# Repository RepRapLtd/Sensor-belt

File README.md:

# Sensor-belt

Device to allow the sense of touch to extend beyond the body.

WIP...

See here for initial details:
  
  https://reprapltd.com/2016/11/15/extra-senses/

Licence: GPL.

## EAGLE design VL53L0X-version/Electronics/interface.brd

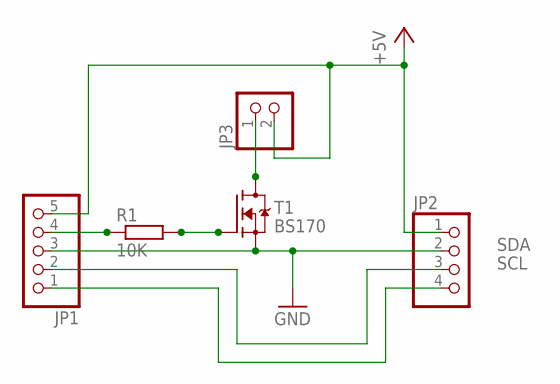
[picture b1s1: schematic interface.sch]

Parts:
JP1: PINHD-1X5; 1X05
JP2: PINHD-1X4; 1X04
JP3: PINHD-1X2; 1X02
R1: 10K; R0805
T1: BS170; SOT23

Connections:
+5V: JP1.5, JP2.1, JP3.2
GND: JP1.3, JP2.2, T1.2 (S)
unnamed: JP1.4, R1.1
unnamed: R1.2, T1.1 (G)
unnamed: JP3.1, T1.3 (D)
unnamed: JP1.2, JP2.3
unnamed: JP1.1, JP2.4

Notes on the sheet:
SDA
SCL

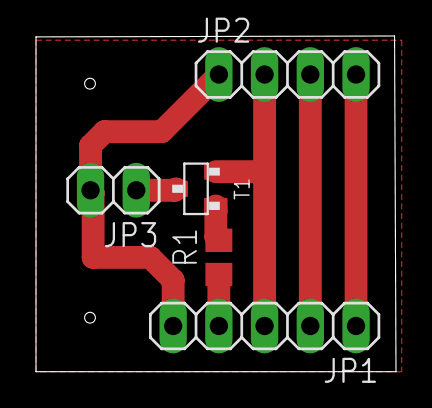
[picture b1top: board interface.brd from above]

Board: 2 copper layers, 20.0 x 18.6 mm, 5 parts (0 on the bottom side), 7 nets.

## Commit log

2016-11-15 Add in the experiments so far...
2016-11-15 GPL licence added.
2016-11-15 Added in FreeCAD model of sensor and vibrator holder.
2016-11-15 Pix added...
2017-11-17 Started experiments with time-of-flight sensor.
2017-11-17 Now with comments...
2018-09-22 Started work on an IR rangefinder version.
2018-10-24 WIP - miniature version...
2019-01-30 File reorganisation
2019-04-25 Started work on the 4 metre sensor.
2019-04-27 1st working version with the VL53L1X 4m sensor.
2019-05-31 LIDAR version coming together...
2024-05-29 Updating
